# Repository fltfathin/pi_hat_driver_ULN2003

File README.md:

# pi_hat_driver_ULN2003

desain driver raspberry pi untuk antarmuka relay dan semacamnya.

desain belum diverifikasi, use at your own risk

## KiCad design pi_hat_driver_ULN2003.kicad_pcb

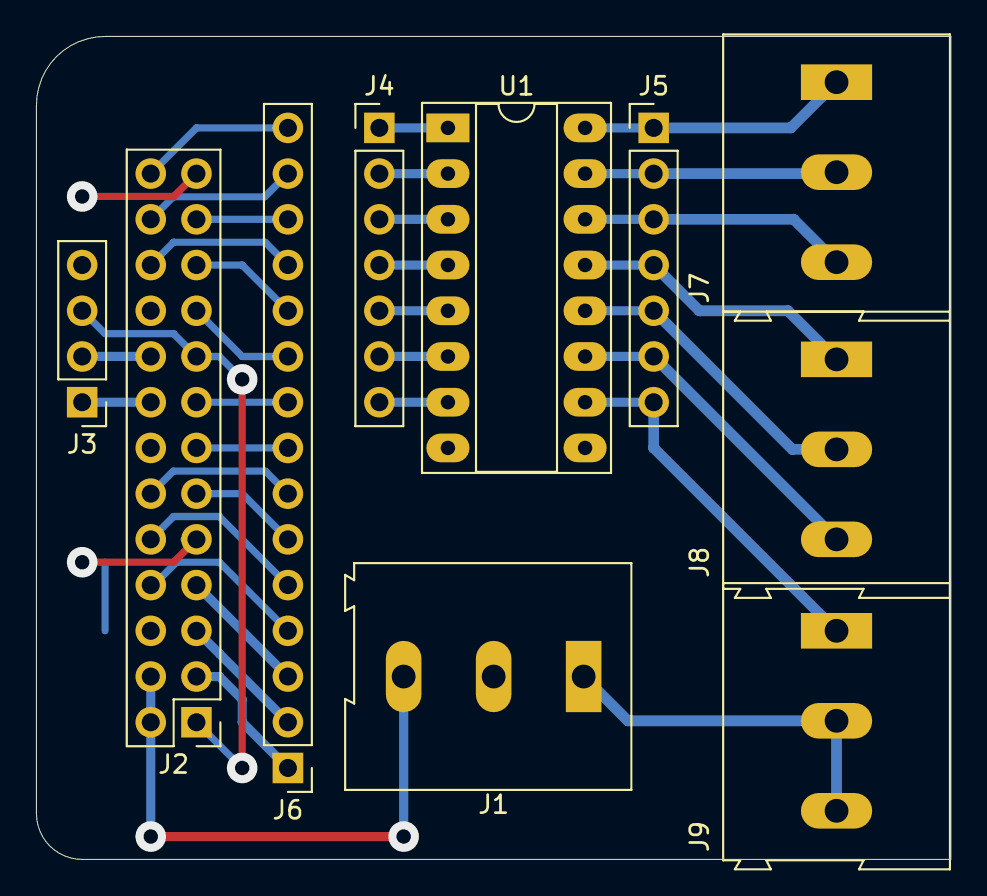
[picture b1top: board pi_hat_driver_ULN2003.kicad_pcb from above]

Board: 2 copper layers, 50.8 x 45.7 mm, 10 parts (0 on the bottom side), 35 nets.

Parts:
J1: supply; TerminalBlock_Altech_AK300-3_P5.00mm
J2: pi_conn; PinHeader_2x13_P2.54mm_Vertical
J3: disp; PinHeader_1x04_P2.54mm_Vertical
J4: drvin; PinHeader_1x07_P2.54mm_Vertical
J5: drvout; PinHeader_1x07_P2.54mm_Vertical
J6: extra_pins; PinHeader_1x15_P2.54mm_Vertical
J7, J8, J9: Conn_01x03; TerminalBlock_Altech_AK300-3_P5.00mm
U1: ULN2003; DIP-16_W7.62mm_Socket_LongPads

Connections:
3V3: J2.1, J2.17, J3.3
5V: J1.3, J2.2, J2.4
GND: J1.2, J2.6, J2.9, J2.14, J2.20, J2.25, J3.4, U1.8, U1.9
unnamed: J2.16, J3.1
unnamed: J2.18, J3.2
unnamed: J4.1, U1.1
unnamed: J5.1, J7.1, U1.16
unnamed: J4.2, U1.2
unnamed: J5.2, J7.2, U1.15
unnamed: J4.3, U1.3
unnamed: J5.3, J7.3, U1.14
unnamed: J4.4, U1.4
unnamed: J5.4, J8.1, U1.13
unnamed: J4.5, U1.5
unnamed: J5.5, J8.2, U1.12
unnamed: J4.6, U1.6
unnamed: J5.6, J8.3, U1.11
unnamed: J4.7, U1.7
unnamed: J5.7, J9.1, U1.10
unnamed: J2.3, J6.1
unnamed: J2.5, J6.2
unnamed: J2.7, J6.3
unnamed: J2.8, J6.4
unnamed: J2.10, J6.5
unnamed: J2.11, J6.6
unnamed: J2.12, J6.7
unnamed: J2.13, J6.8
unnamed: J2.15, J6.9
unnamed: J2.19, J6.10
unnamed: J2.21, J6.11
unnamed: J2.22, J6.12
unnamed: J2.23, J6.13
unnamed: J2.24, J6.14
unnamed: J2.26, J6.15
VREL: J1.1, J9.2, J9.3

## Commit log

2020-06-10 made PTH single-sided version
